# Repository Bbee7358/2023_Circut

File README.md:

# 2023_Circut

このリポジトリは僕がどっか行っている間にソフト班やハード班がこまらないように一応今年作ってきた回路をアップしました。

**しおからへ**

もしTeensy4.1のピンでどこのピンが空いていて、使えるのか知りたいときは

2022_029 > Main_BoardV1.brd

を開けるとどこのピンがつながっているかわかるから、それとTeensy4.1のピン配置をネットから調べてきて、照らし合わせてみたら、どのピンを使えばいいかわかるで。

**まっかさへ**

もしロボットの部品を作るときに基板の寸法とかで困ったら、このリポジトリのデータから自分が気になる基板をEAGLEで開いて、fusion360に書き出す(exportする)と寸法とか実物の大きさがわかるようになるで。
書き出し方とかは自分でわかりやすいサイト見つけてやってくれたらいいけど、一応自分がわかりやすいな、って思ったサイトを載せとくから近道したかったらみてみて

[EAGLEからFUSION360へデータの書き出し方法](https://westgate-lab.hatenablog.com/entry/2020/05/09/180639)

↑このサイトいろいろエクスポート方法以外に違うことも書いてるけどそこは自分で無視してみてみて

**現在使ってる基板の所在地**

電源兼モタドラ基板

2022_12 > dengenn.brd

2022_12 > dengenn_top.brd

メイン基板

2022_029 > Main_BoardV1.brd

ライン基板

2022_029 > angrlline6.brd

ボール基板

2022_029 > V9.brd

**フォルダのダウンロード方法**
で、たぶんこのリポジトリ内のファイルのダウンロードの仕方はわかると思うけど一応サイト載せとくから頑張ってダウンロードしてみて

[Githubリポジトリのダウンロードの仕方](http://www.humblesoft.com/wiki/?GitHub%E3%81%8B%E3%82%89%E3%83%80%E3%82%A6%E3%83%B3%E3%83%AD%E3%83%BC%E3%83%89%E3%81%99%E3%82%8B%E6%96%B9%E6%B3%95#o8a06f02)

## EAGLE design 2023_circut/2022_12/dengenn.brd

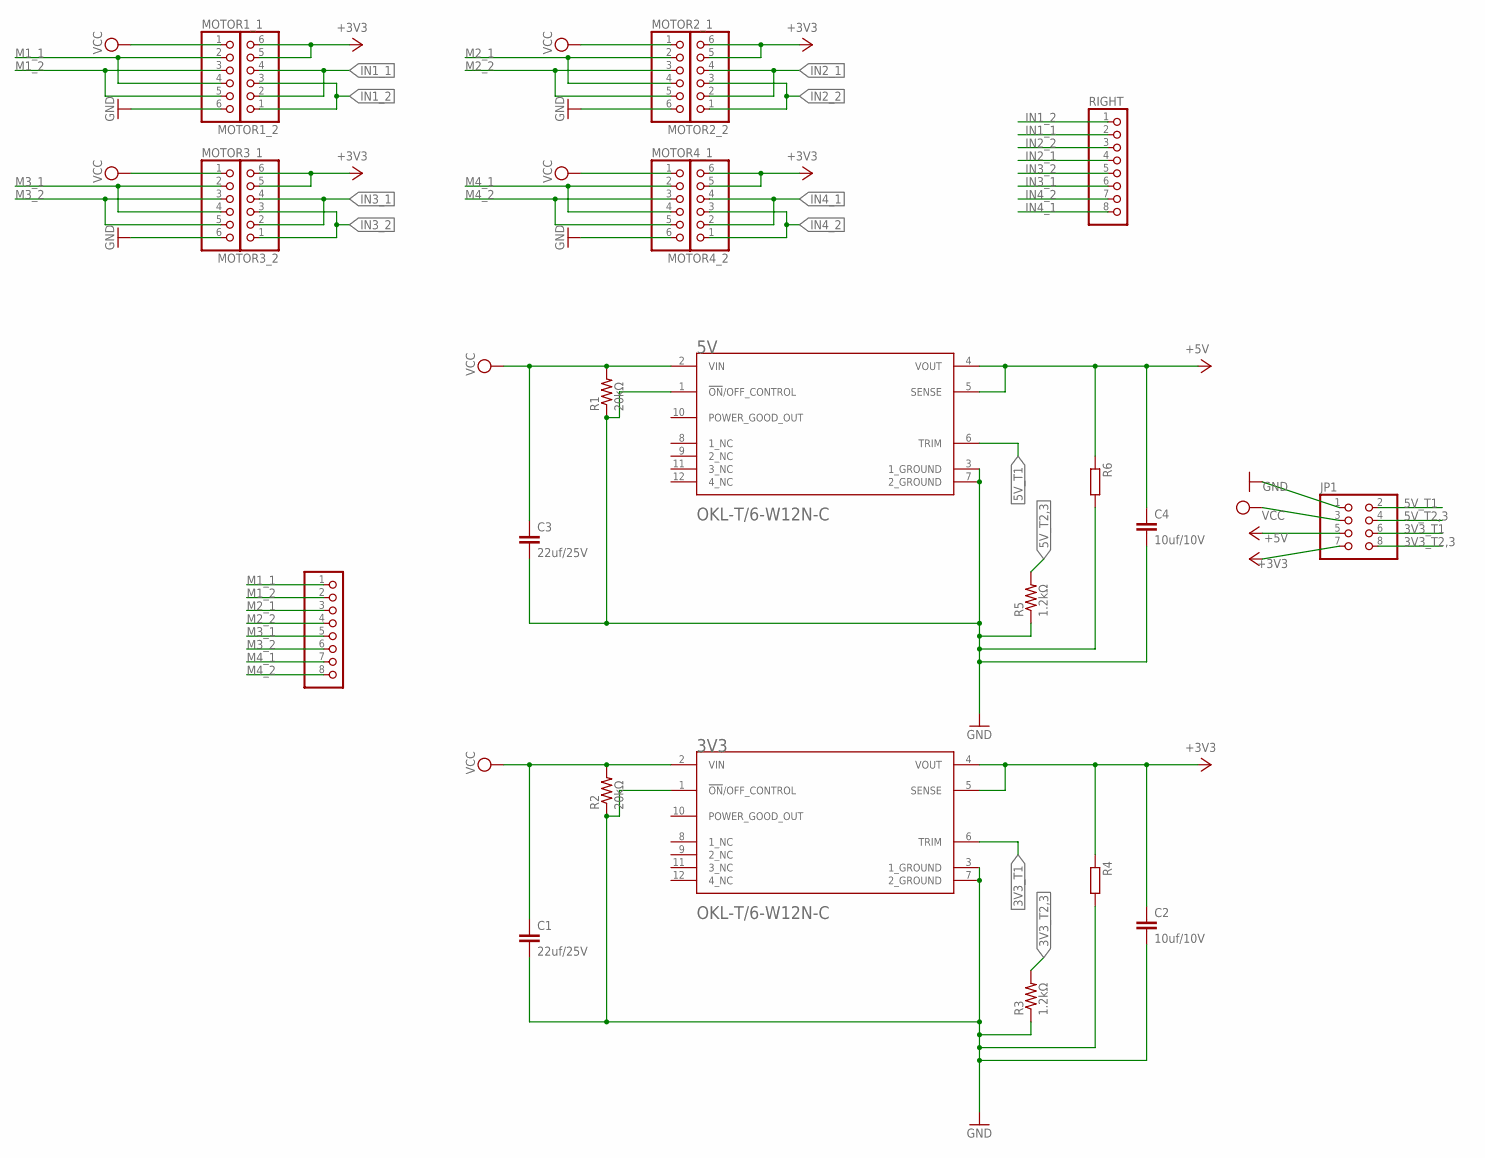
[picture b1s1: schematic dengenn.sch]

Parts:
3V3, 5V: OKL-T/6-W12N-CMURATA_OKL-T-6-W12N-C_0_0; MURATA_OKL-T-6-W12N-C_0
C1, C3: 22uf/25V; C1206
C2, C4: 10uf/10V; C0603
JP1: PINHD-2X4; 2X04
LEFT: PINHD-1X8; 1X08
MOTOR1_1, MOTOR1_2, MOTOR2_1, MOTOR2_2, MOTOR3_1, MOTOR3_2, MOTOR4_1, MOTOR4_2: PINHD-1X06_2.54-S; 1X06-S
R1, R2: 20kΩ; R0603
R3, R5: 1.2kΩ; R0603
R4, R6: R-EU_0309/12; 0309/12
RIGHT: PINHD-1X8; 1X08

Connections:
3V3_T1: 3V3.6 (TRIM), JP1.6
3V3_T2,3: JP1.8, R3.2
5V_T1: 5V.6 (TRIM), JP1.2
5V_T2,3: JP1.4, R5.2
+3V3: 3V3.4 (VOUT), 3V3.5 (SENSE), C2.1, JP1.7, MOTOR1_2.5, MOTOR1_2.6, MOTOR2_2.5, MOTOR2_2.6, MOTOR3_2.5, MOTOR3_2.6, MOTOR4_2.5, MOTOR4_2.6, R4.1
+5V: 5V.4 (VOUT), 5V.5 (SENSE), C4.1, JP1.5, R6.1
GND: 3V3.1 (!ON!/OFF_CONTROL), 3V3.3 (1_GROUND), 3V3.7 (2_GROUND), 5V.1 (!ON!/OFF_CONTROL), 5V.3 (1_GROUND), 5V.7 (2_GROUND), C1.2, C2.2, C3.2, C4.2, JP1.1, MOTOR1_1.6, MOTOR2_1.6, MOTOR3_1.6, MOTOR4_1.6, R1.1, R2.1, R3.1, R4.2, R5.1, R6.2
IN1_1: MOTOR1_2.2, MOTOR1_2.4, RIGHT.2
IN1_2: MOTOR1_2.1, MOTOR1_2.3, RIGHT.1
IN2_1: MOTOR2_2.2, MOTOR2_2.4, RIGHT.4
IN2_2: MOTOR2_2.1, MOTOR2_2.3, RIGHT.3
IN3_1: MOTOR3_2.2, MOTOR3_2.4, RIGHT.6
IN3_2: MOTOR3_2.1, MOTOR3_2.3, RIGHT.5
IN4_1: MOTOR4_2.2, MOTOR4_2.4, RIGHT.8
IN4_2: MOTOR4_2.1, MOTOR4_2.3, RIGHT.7
M1_1: LEFT.1, MOTOR1_1.2, MOTOR1_1.4
M1_2: LEFT.2, MOTOR1_1.3, MOTOR1_1.5
M2_1: LEFT.3, MOTOR2_1.2, MOTOR2_1.4
M2_2: LEFT.4, MOTOR2_1.3, MOTOR2_1.5
M3_1: LEFT.5, MOTOR3_1.2, MOTOR3_1.4
M3_2: LEFT.6, MOTOR3_1.3, MOTOR3_1.5
M4_1: LEFT.7, MOTOR4_1.2, MOTOR4_1.4
M4_2: LEFT.8, MOTOR4_1.3, MOTOR4_1.5
VCC: 3V3.2 (VIN), 5V.2 (VIN), C1.1, C3.1, JP1.3, MOTOR1_1.1, MOTOR2_1.1, MOTOR3_1.1, MOTOR4_1.1, R1.2, R2.2

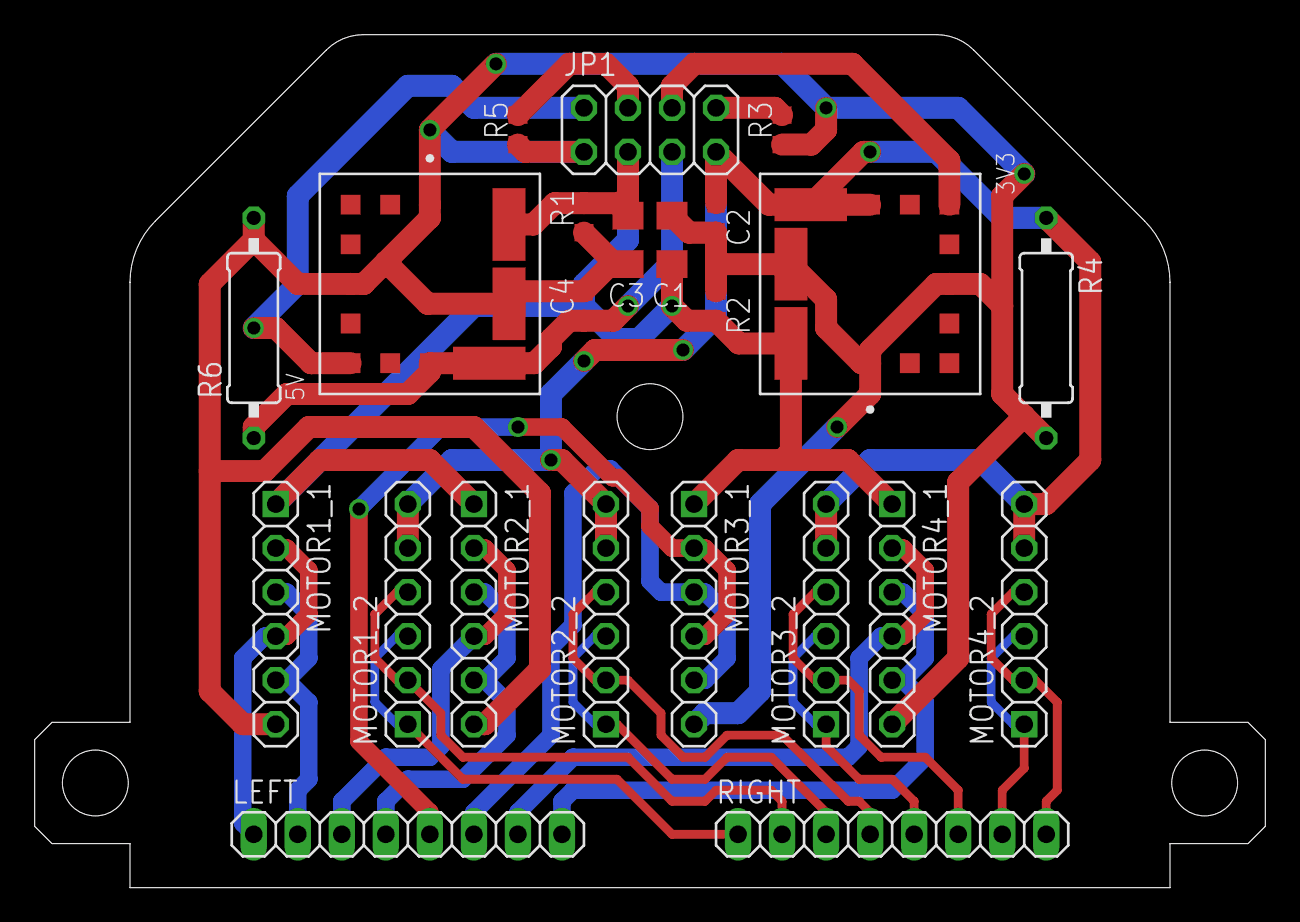
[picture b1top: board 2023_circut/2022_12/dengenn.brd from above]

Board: 2 copper layers, 71.0 x 49.2 mm, 23 parts (0 on the bottom side), 24 nets.

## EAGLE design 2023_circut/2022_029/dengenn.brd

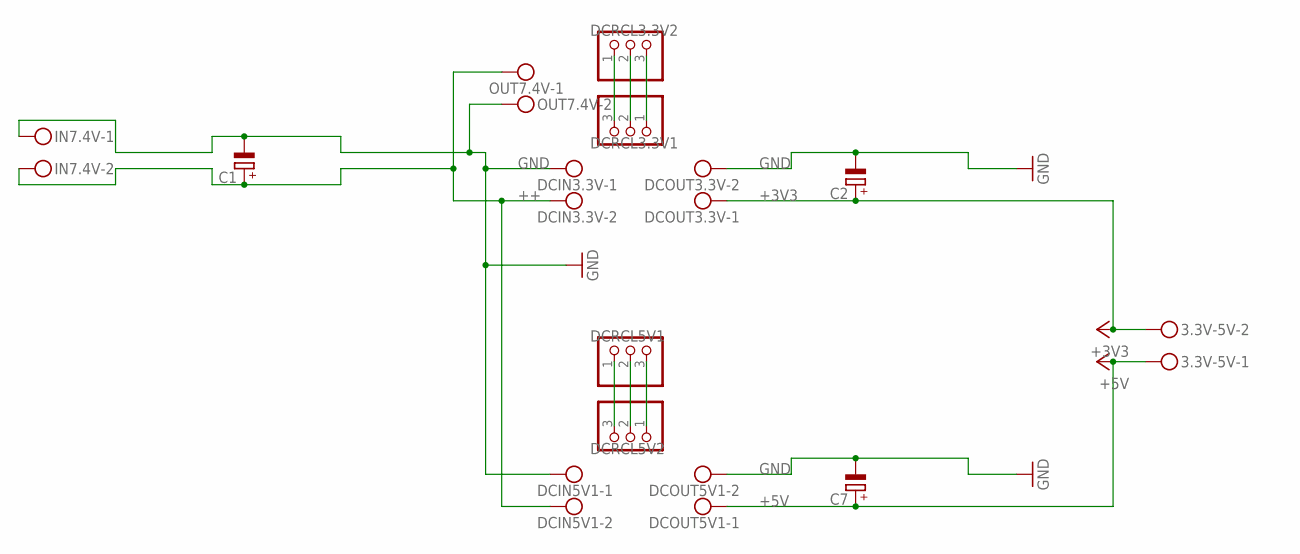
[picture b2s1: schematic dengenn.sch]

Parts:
3.3V-5V: MKDSN1,5/2-5,08
C1, C2, C7: CPOL-EUE5-10.5; E5-10,5
DCIN3.3V, DCIN5V1: MKDSN1,5/2-5,08
DCOUT3.3V, DCOUT5V1: MKDSN1,5/2-5,08
DCRCL3.3V1, DCRCL3.3V2, DCRCL5V1, DCRCL5V2: PINHD-1X3; 1X03
IN7.4V: MKDSN1,5/2-5,08
OUT7.4V: MKDSN1,5/2-5,08

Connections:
+3V3: 3.3V-5V.2, C2.+, DCOUT3.3V.1
+5V: 3.3V-5V.1, C7.+, DCOUT5V1.1
++: C1.+, DCIN3.3V.2, DCIN5V1.2, IN7.4V.2, OUT7.4V.1
GND: C1.-, C2.-, C7.-, DCIN3.3V.1, DCIN5V1.1, DCOUT3.3V.2, DCOUT5V1.2, IN7.4V.1, OUT7.4V.2
unnamed: DCRCL3.3V1.3, DCRCL3.3V2.1
unnamed: DCRCL3.3V1.2, DCRCL3.3V2.2
unnamed: DCRCL3.3V1.1, DCRCL3.3V2.3
unnamed: DCRCL5V1.1, DCRCL5V2.3
unnamed: DCRCL5V1.2, DCRCL5V2.2
unnamed: DCRCL5V1.3, DCRCL5V2.1

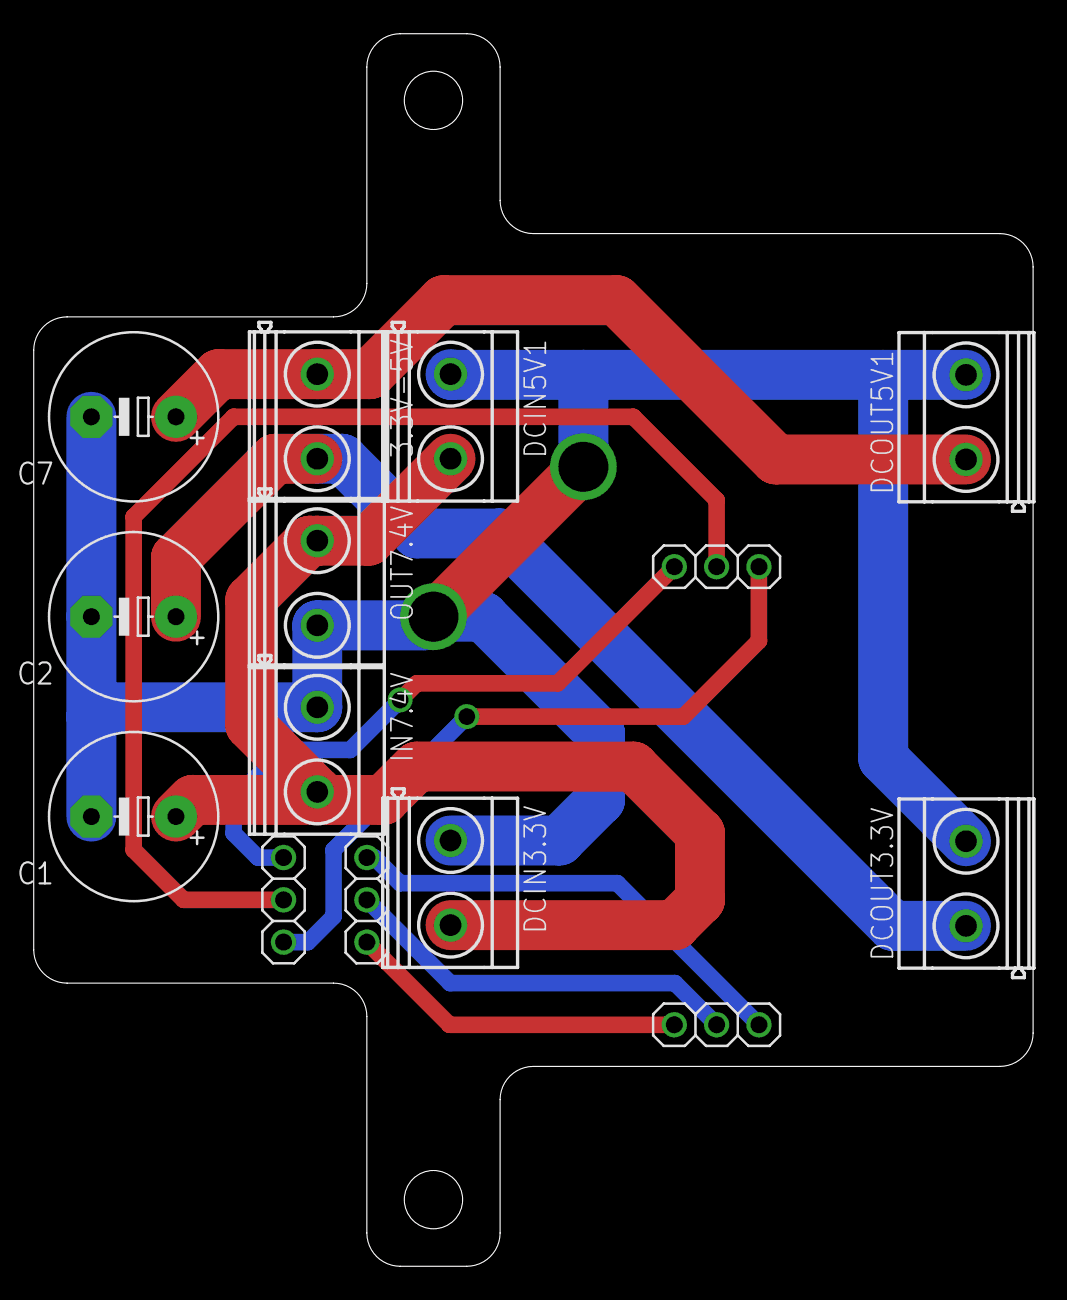
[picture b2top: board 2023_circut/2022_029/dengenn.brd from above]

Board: 2 copper layers, 60.0 x 74.0 mm, 14 parts (0 on the bottom side), 10 nets.

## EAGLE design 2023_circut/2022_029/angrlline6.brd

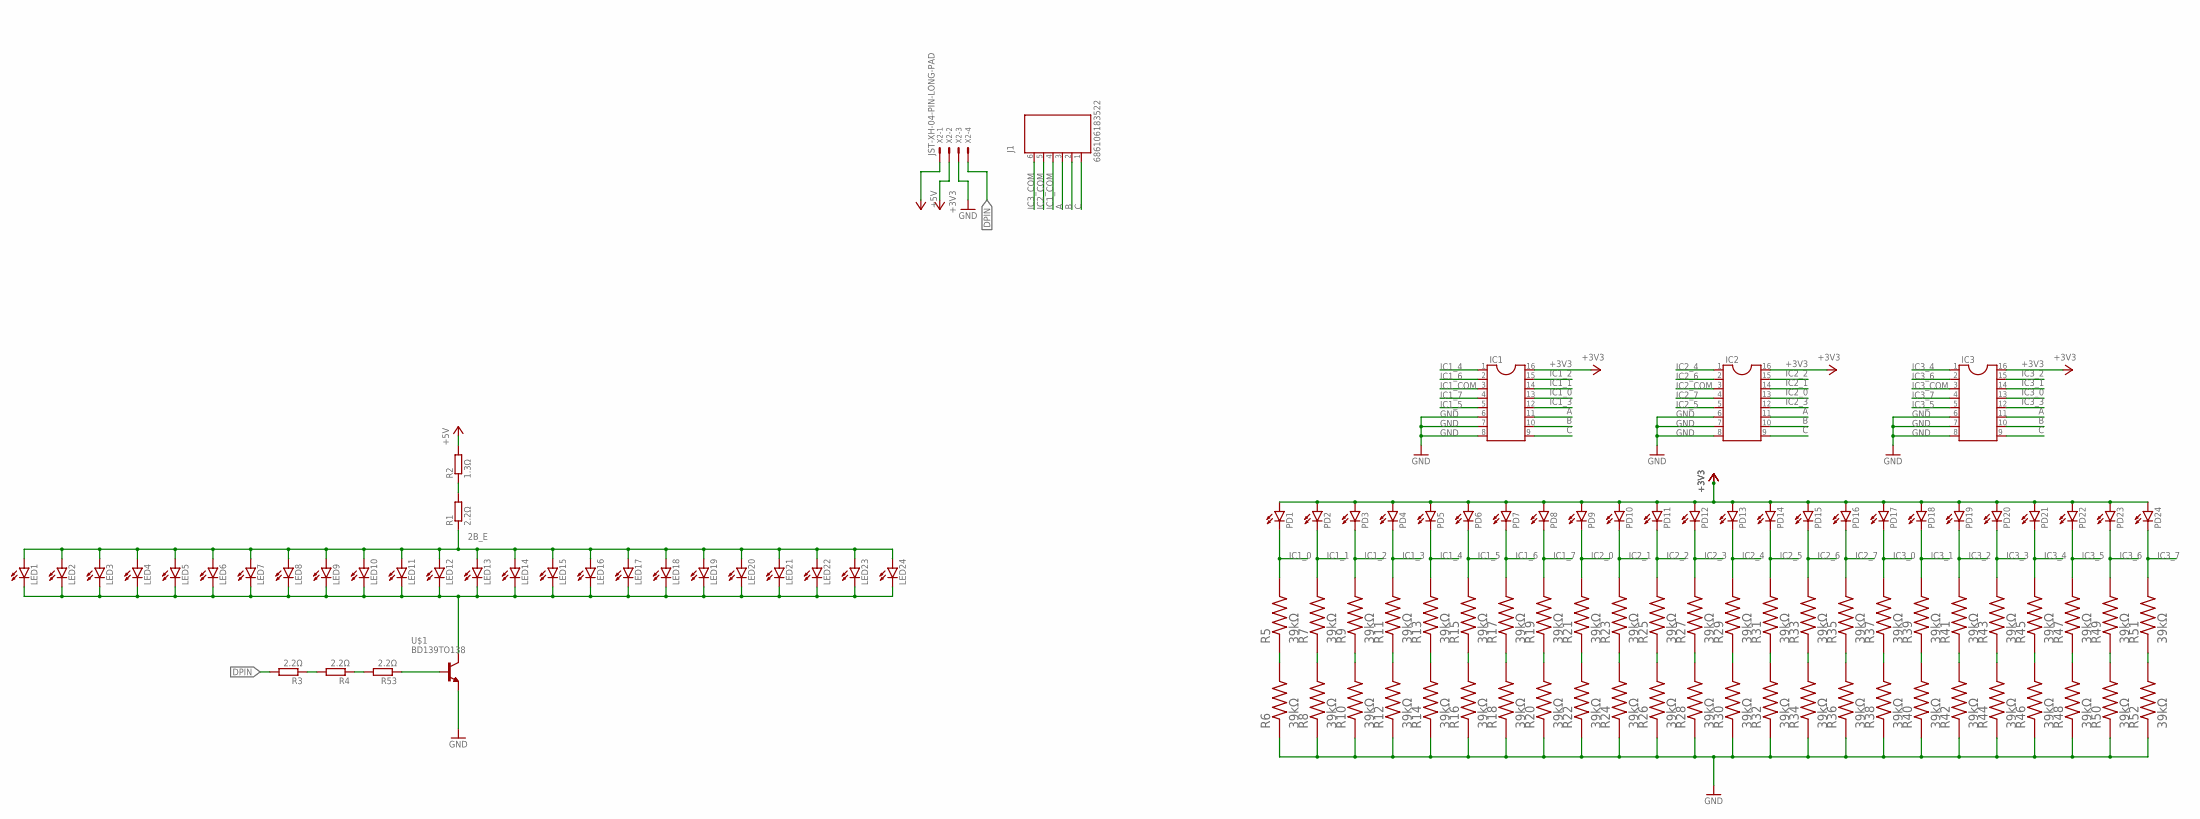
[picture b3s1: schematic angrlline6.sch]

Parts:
IC1, IC2, IC3: DIL16
J1: 686106183522
LED1, LED2, LED3, LED4, LED5, LED6, LED7, LED8, LED9, LED10, LED11, LED12, LED13, LED14, LED15, LED16, LED17, LED18, LED19, LED20, LED21, LED22, LED23, LED24: LED3MM
PD1, PD2, PD3, PD4, PD5, PD6, PD7, PD8, PD9, PD10, PD11, PD12, PD13, PD14, PD15, PD16, PD17, PD18, PD19, PD20, PD21, PD22, PD23, PD24: LED3MM
R1, R3, R4, R53: 2.2Ω; 0207/10
R2: 1.3Ω; 0207/10
R5, R6, R7, R8, R9, R10, R11, R12, R13, R14, R15, R16, R17, R18, R19, R20, R21, R22, R23, R24, R25, R26, R27, R28, R29, R30, R31, R32, R33, R34, R35, R36, R37, R38, R39, R40, R41, R42, R43, R44, R45, R46, R47, R48, R49, R50, R51, R52: 39kΩ; RESC1608X55N
U$1: BD139TO138; TO126
X2: JST-XH-04-PIN-LONG-PAD; JST-XH-04-PACKAGE-LONG-PAD

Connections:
2B_E: LED1.A, LED2.A, LED3.A, LED4.A, LED5.A, LED6.A, LED7.A, LED8.A, LED9.A, LED10.A, LED11.A, LED12.A, LED13.A, LED14.A, LED15.A, LED16.A, LED17.A, LED18.A, LED19.A, LED20.A, LED21.A, LED22.A, LED23.A, LED24.A, R1.1
+3V3: IC1.16, IC2.16, IC3.16, PD1.A, PD2.A, PD3.A, PD4.A, PD5.A, PD6.A, PD7.A, PD8.A, PD9.A, PD10.A, PD11.A, PD12.A, PD13.A, PD14.A, PD15.A, PD16.A, PD17.A, PD18.A, PD19.A, PD20.A, PD21.A, PD22.A, PD23.A, PD24.A, X2.2
+5V: R2.2, X2.1
A: IC1.11, IC2.11, IC3.11, J1.3 (4)
B: IC1.10, IC2.10, IC3.10, J1.2 (5)
BASE: R53.1, U$1.B
C: IC1.9, IC2.9, IC3.9, J1.1 (6)
DPIN: R3.2, X2.4
ENCODE: LED1.K (C), LED2.K (C), LED3.K (C), LED4.K (C), LED5.K (C), LED6.K (C), LED7.K (C), LED8.K (C), LED9.K (C), LED10.K (C), LED11.K (C), LED12.K (C), LED13.K (C), LED14.K (C), LED15.K (C), LED16.K (C), LED17.K (C), LED18.K (C), LED19.K (C), LED20.K (C), LED21.K (C), LED22.K (C), LED23.K (C), LED24.K (C), U$1.C
GND: IC1.6, IC1.7, IC1.8, IC2.6, IC2.7, IC2.8, IC3.6, IC3.7, IC3.8, R6.1, R8.1, R10.1, R12.1, R14.1, R16.1, R18.1, R20.1, R22.1, R24.1, R26.1, R28.1, R30.1, R32.1, R34.1, R36.1, R38.1, R40.1, R42.1, R44.1, R46.1, R48.1, R50.1, R52.1, U$1.E, X2.3
IC1_0: IC1.13, PD1.K (C), R5.2
IC1_1: IC1.14, PD2.K (C), R7.2
IC1_2: IC1.15, PD3.K (C), R9.2
IC1_3: IC1.12, PD4.K (C), R11.2
IC1_4: IC1.1, PD5.K (C), R13.2
IC1_5: IC1.5, PD6.K (C), R15.2
IC1_6: IC1.2, PD7.K (C), R17.2
IC1_7: IC1.4, PD8.K (C), R19.2
IC1_COM: IC1.3, J1.4 (3)
IC2_0: IC2.13, PD9.K (C), R21.2
IC2_1: IC2.14, PD10.K (C), R23.2
IC2_2: IC2.15, PD11.K (C), R25.2
IC2_3: IC2.12, PD12.K (C), R27.2
IC2_4: IC2.1, PD13.K (C), R29.2
IC2_5: IC2.5, PD14.K (C), R31.2
IC2_6: IC2.2, PD15.K (C), R33.2
IC2_7: IC2.4, PD16.K (C), R35.2
IC2_COM: IC2.3, J1.5 (2)
IC3_0: IC3.13, PD17.K (C), R37.2
IC3_1: IC3.14, PD18.K (C), R39.2
IC3_2: IC3.15, PD19.K (C), R41.2
IC3_3: IC3.12, PD20.K (C), R43.2
IC3_4: IC3.1, PD21.K (C), R45.2
IC3_5: IC3.5, PD22.K (C), R47.2
IC3_6: IC3.2, PD23.K (C), R49.2
IC3_7: IC3.4, PD24.K (C), R51.2
IC3_COM: IC3.3, J1.6 (1)
unnamed: R1.2, R2.1
unnamed: R7.1, R8.2
unnamed: R9.1, R10.2
unnamed: R11.1, R12.2
unnamed: R13.1, R14.2
unnamed: R15.1, R16.2
unnamed: R17.1, R18.2
unnamed: R19.1, R20.2
unnamed: R21.1, R22.2
unnamed: R23.1, R24.2
unnamed: R25.1, R26.2
unnamed: R27.1, R28.2
unnamed: R29.1, R30.2
unnamed: R5.1, R6.2
unnamed: R4.1, R53.2
unnamed: R3.1, R4.2
unnamed: R31.1, R32.2
unnamed: R33.1, R34.2
unnamed: R35.1, R36.2
unnamed: R37.1, R38.2
unnamed: R39.1, R40.2
unnamed: R41.1, R42.2
unnamed: R43.1, R44.2
unnamed: R45.1, R46.2
unnamed: R47.1, R48.2
unnamed: R49.1, R50.2
unnamed: R51.1, R52.2

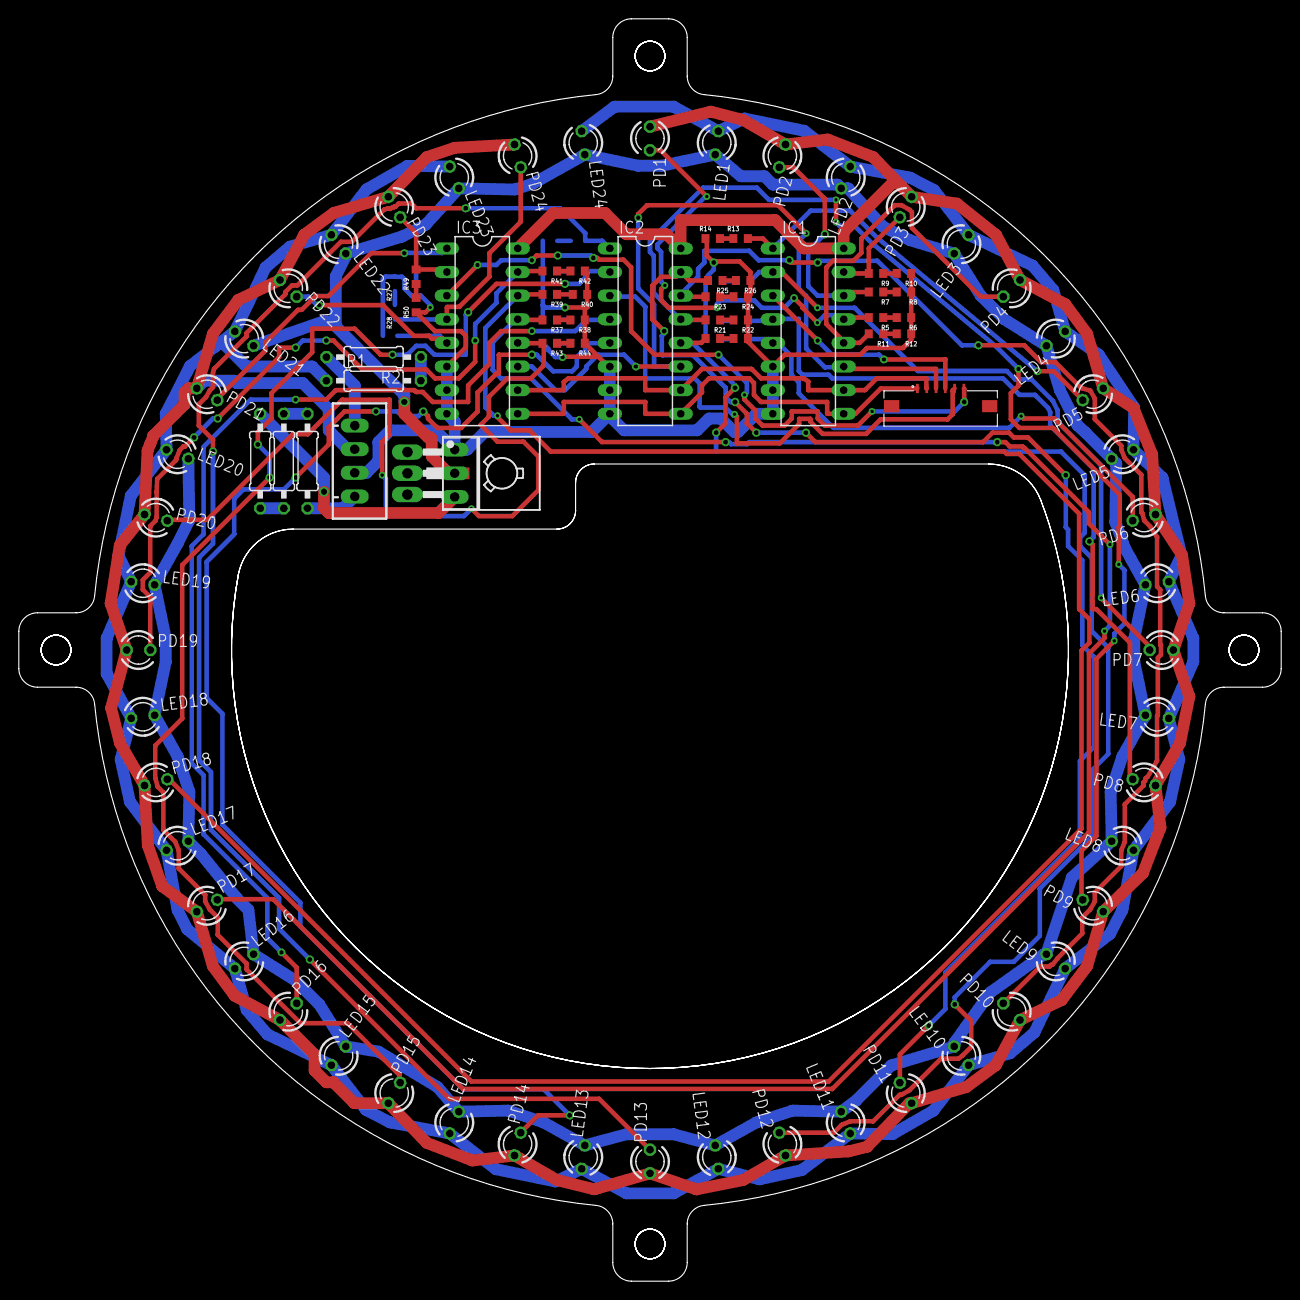
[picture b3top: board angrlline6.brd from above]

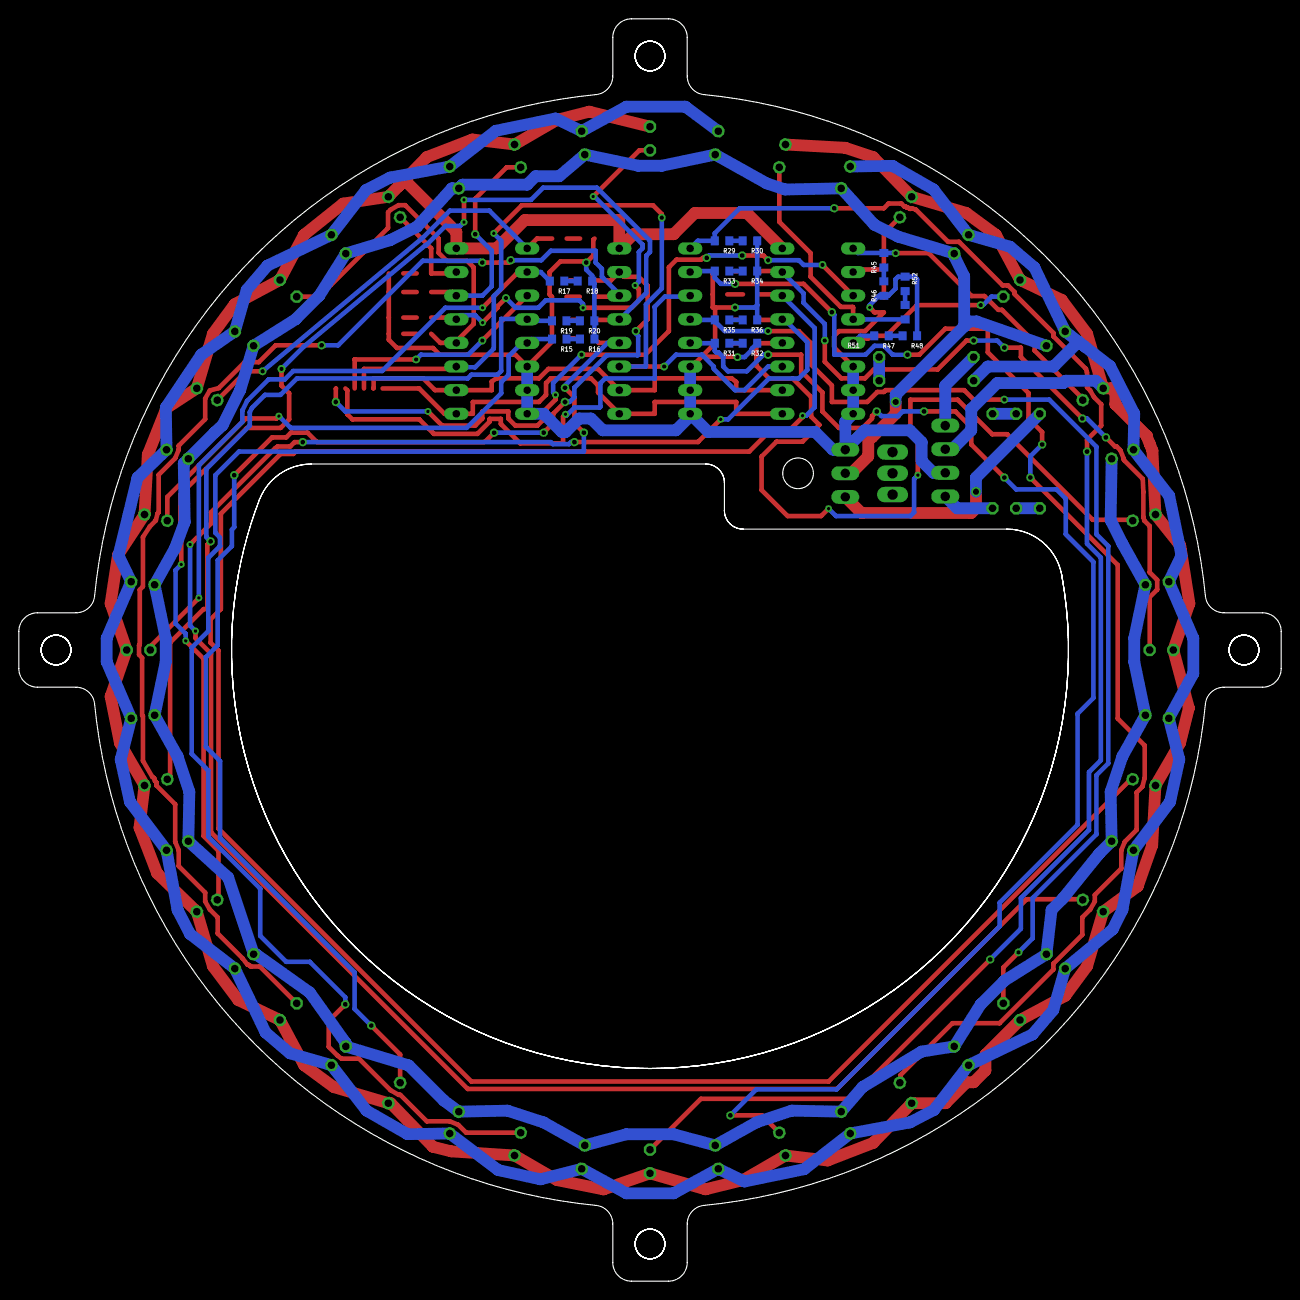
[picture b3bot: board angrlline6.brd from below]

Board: 2 copper layers, 135.7 x 135.7 mm, 107 parts (20 on the bottom side), 64 nets.

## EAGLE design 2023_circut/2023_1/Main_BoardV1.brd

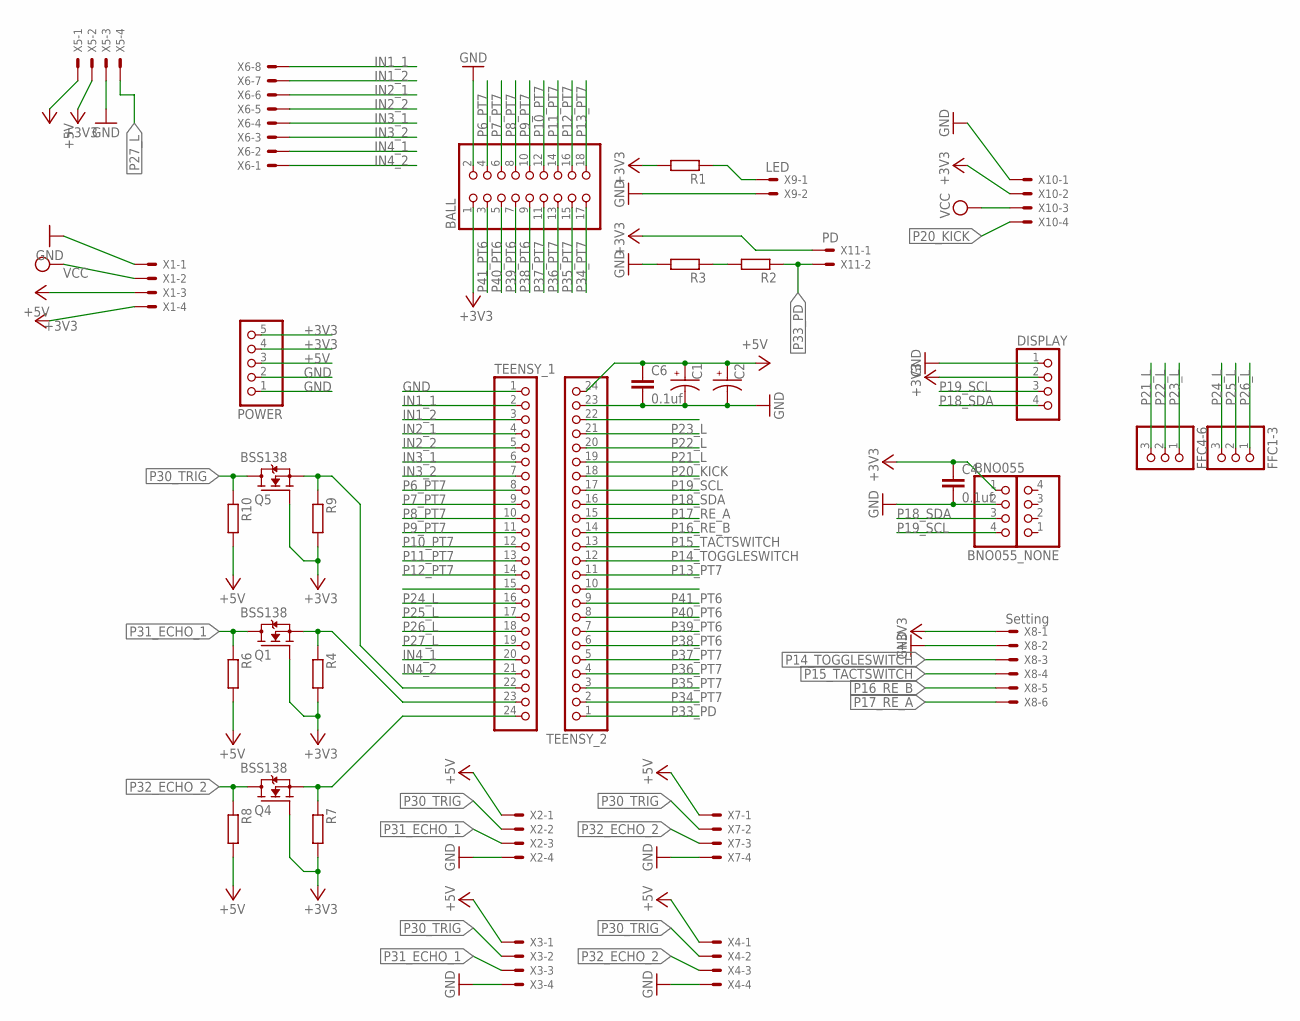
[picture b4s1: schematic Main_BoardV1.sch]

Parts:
BALL: PINHD-2X9; 2X09
BNO055, BNO055_NONE: PINHD-1X4; 1X04
C1, C2: EEEFK1E332AM; CAP_EEEFK1E332AM
C4, C6: 0.1uf; C0603
DISPLAY: PINHD-1X04_2.54-S; 1X04-S
FFC1-3, FFC4-6: PINHD-1X03_2.54-S; 1X03-S
POWER: PINHD-1X05_2.54-S; 1X05-S
Q1, Q4, Q5: BSS138; SOT95P240X111-3N
R1, R2, R3, R4, R6, R7, R8, R9, R10: R-EU_R0603; R0603
TEENSY_1, TEENSY_2: PINHD-1X24; 1X24
X1: Power; JST-XH-04-PACKAGE-LONG-PAD
X2, X3, X4, X7: JST-XH-04-PIN-LONG-PAD; JST-XH-04-PACKAGE-LONG-PAD
X5: JST-XH-04-PIN-ROUND-PAD; JST-XH-04-PACKAGE-ROUND-PAD
X6: Motor; JST-XH-08-PACKAGE-ROUND-PAD
X8: Setting; JST-XH-06-PACKAGE-ROUND-PAD
X9: LED; JST-XH-02-PACKAGE-ROUND-PAD
X10: Kicker; JST-XH-04-PACKAGE-ROUND-PAD
X11: PD; JST-XH-02-PACKAGE-ROUND-PAD

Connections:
+3V3: BALL.1, BNO055.1, C4.1, DISPLAY.2, POWER.4, POWER.5, Q1.1 (G), Q4.1 (G), Q5.1 (G), R1.2, R4.2, R7.2, R9.2, X1.4, X5.2, X8.1, X10.2, X11.1
+5V: C1.1, C2.1, C6.1, POWER.3, R6.2, R8.2, R10.2, TEENSY_2.24, X1.3, X2.1, X3.1, X4.1, X5.1, X7.1
GND: BALL.2, BNO055.2, C1.2, C2.2, C4.2, C6.2, DISPLAY.1, POWER.1, POWER.2, R3.2, TEENSY_1.1, TEENSY_2.23, X1.1, X2.4, X3.4, X4.4, X5.3, X7.4, X8.2, X9.2, X10.1
IN1_1: TEENSY_1.2, X6.8
IN1_2: TEENSY_1.3, X6.7
IN2_1: TEENSY_1.4, X6.6
IN2_2: TEENSY_1.5, X6.5
IN3_1: TEENSY_1.6, X6.4
IN3_2: TEENSY_1.7, X6.3
IN4_1: TEENSY_1.20, X6.2
IN4_2: TEENSY_1.21, X6.1
unnamed: R1.1, X9.1
unnamed: R2.2, R3.1
unnamed: Q1.2 (S), R4.1, TEENSY_1.23
unnamed: Q4.2 (S), R7.1, TEENSY_1.24
unnamed: Q5.2 (S), R9.1, TEENSY_1.22
P6_PT7: BALL.4, TEENSY_1.8
P7_PT7: BALL.6, TEENSY_1.9
P8_PT7: BALL.8, TEENSY_1.10
P9_PT7: BALL.10, TEENSY_1.11
P10_PT7: BALL.12, TEENSY_1.12
P11_PT7: BALL.14, TEENSY_1.13
P12_PT7: BALL.16, TEENSY_1.14
P13_PT7: BALL.18, TEENSY_2.11
P14_TOGGLESWITCH: TEENSY_2.12, X8.3
P15_TACTSWITCH: TEENSY_2.13, X8.4
P16_RE_B: TEENSY_2.14, X8.5
P17_RE_A: TEENSY_2.15, X8.6
P18_SDA: BNO055.3, DISPLAY.4, TEENSY_2.16
P19_SCL: BNO055.4, DISPLAY.3, TEENSY_2.17
P20_KICK: TEENSY_2.18, X10.4
P21_L: FFC4-6.3, TEENSY_2.19
P22_L: FFC4-6.2, TEENSY_2.20
P23_L: FFC4-6.1, TEENSY_2.21
P24_L: FFC1-3.3, TEENSY_1.16
P25_L: FFC1-3.2, TEENSY_1.17
P26_L: FFC1-3.1, TEENSY_1.18
P27_L: TEENSY_1.19, X5.4
P30_TRIG: Q5.3 (D), R10.1, X2.2, X3.2, X4.2, X7.2
P31_ECHO_1: Q1.3 (D), R6.1, X2.3, X3.3
P32_ECHO_2: Q4.3 (D), R8.1, X4.3, X7.3
P33_PD: R2.1, TEENSY_2.1, X11.2
P34_PT7: BALL.17, TEENSY_2.2
P35_PT7: BALL.15, TEENSY_2.3
P36_PT7: BALL.13, TEENSY_2.4
P37_PT7: BALL.11, TEENSY_2.5
P38_PT6: BALL.9, TEENSY_2.6
P39_PT6: BALL.7, TEENSY_2.7
P40_PT6: BALL.5, TEENSY_2.8
P41_PT6: BALL.3, TEENSY_2.9
VCC: X1.2, X10.3

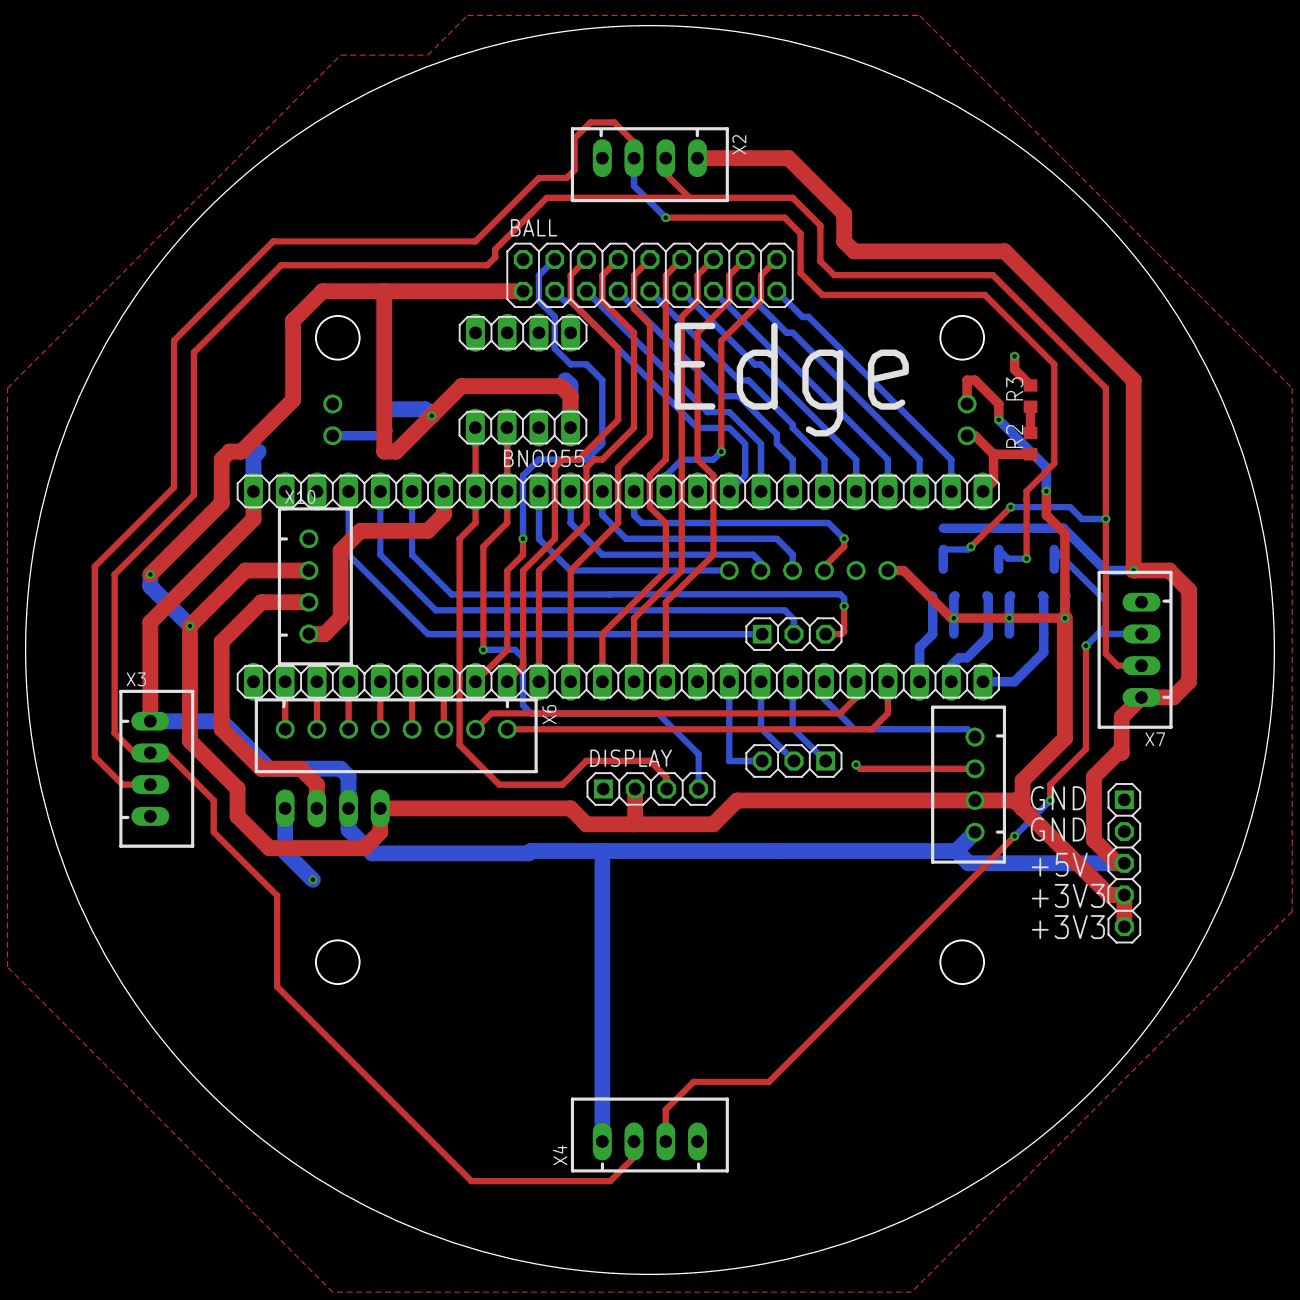
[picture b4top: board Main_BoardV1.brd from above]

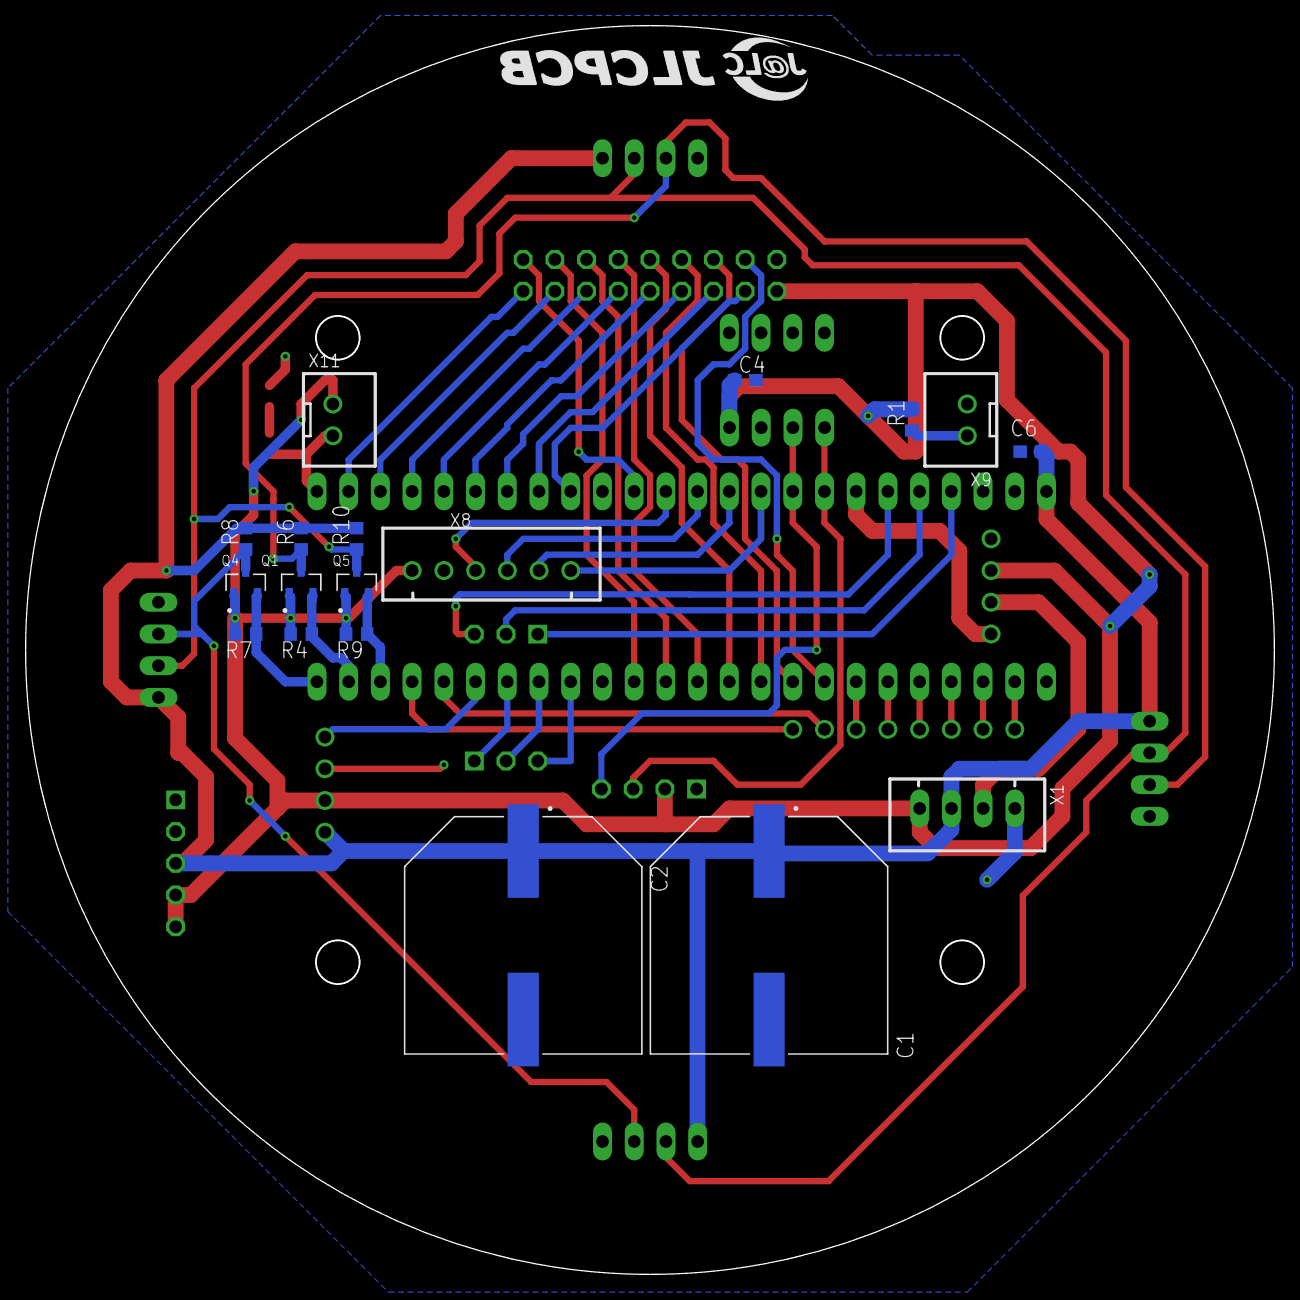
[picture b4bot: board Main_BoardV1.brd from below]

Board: 2 copper layers, 100.0 x 100.0 mm, 36 parts (18 on the bottom side), 51 nets.
